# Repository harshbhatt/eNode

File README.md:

# Notes
* Current project files under `Hardware` folder
* Some resistors and capacitors (imported from the photon) don't have a "box" silkscreen in their footprint - for the final batch, these footprints are better omitted.
* RF components have been placed using the photon as reference
  * (X,Y) coords for RF components have been taken from reference design then moved as a group to maintain relative positioning
* (X,Y) coords for the remaining major components can be referenced from V2
* Make sure to use the 4-layer DRC from spark (under photon\cam-drc\spark-4layer.dru)
* Keep all traces at **12mils** unless absolutely needed

# To-Do
* Change MEMs mic to Condenser mic
* Ground plane vias for RF
* Determine good location for RGB LED
* Copy keepout & fill polygons from V2.2 and photon reference
* Source a SMT LDR?
* All remaining RLC footprints can be replaced with the footprints used by spark, or the master library can be updated

* Possibly shorten overall length of sensor -> if all components fit

# General Guide
* Don't commit library, board and schematic backup files auto generated by Eagle (should be taken care of, by the included .gitignore file, but just fyi)
* Look at V2.2 & photon for reference (Under reference drawings folder)
* Make sure you set your library path to the `Libraries` folder under `Options->Directories` in Eagle

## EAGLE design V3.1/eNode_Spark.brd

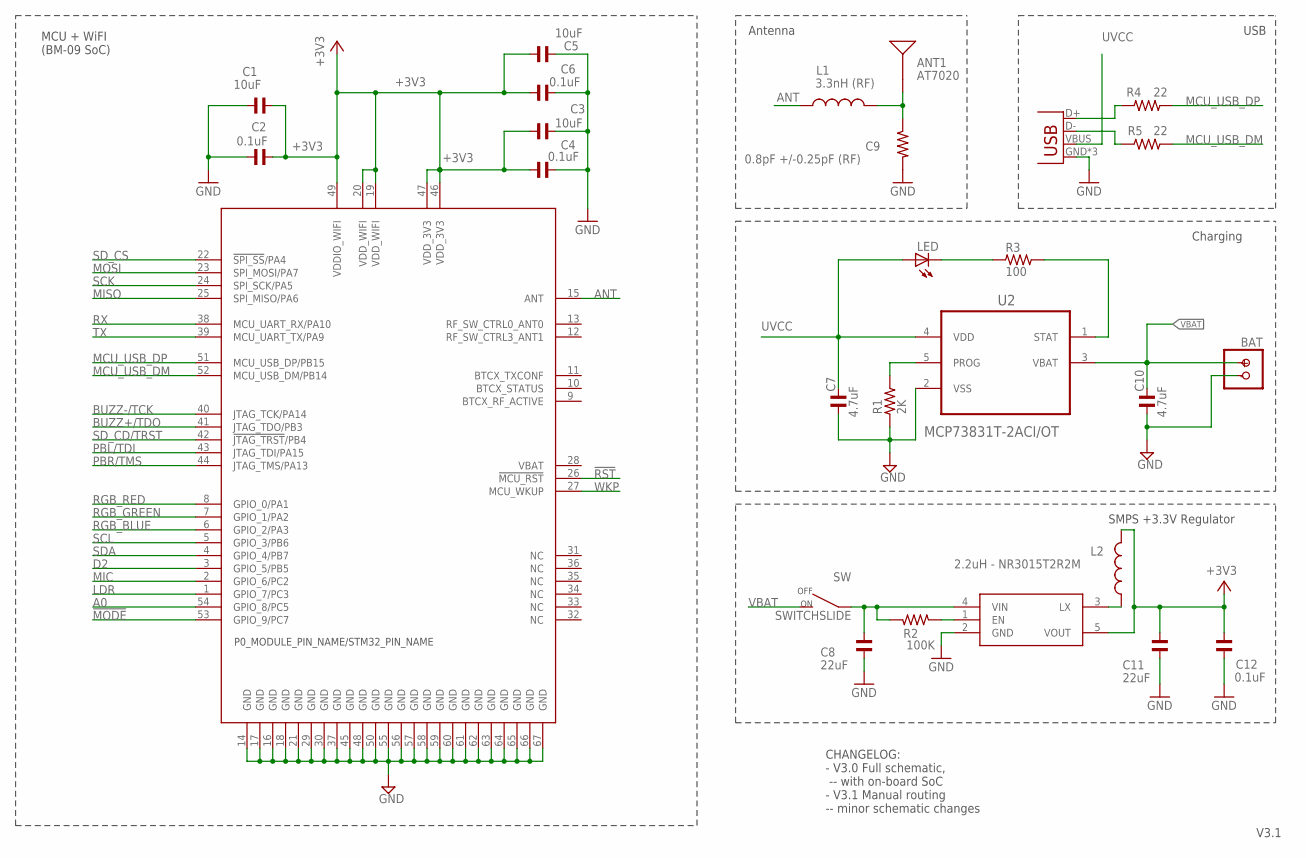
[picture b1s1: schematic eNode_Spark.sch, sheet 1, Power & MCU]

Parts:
ANT1: AT7020
BAT: BATTERYSMT; JST-2-SMD
C1, C3, C5: 10uF; C0402
C2, C4, C6, C12: 0.1uF; C0402
C7, C10: 4.7uF; C0402
C8, C11: 22uF; C0603
C9: 0.8pF +/-0.25pF (RF); R0402_B
L1: 3.3nH (RF); L0402_B
L2: 2.2uH - NR3015T2R2M; INDUCTOR-NR3015
LED: LED; RA_SMD_LED
R1: 2K; R0603
R2: 100K; R0402
R3: 100; R0603
R4, R5: 22; R0402
SW: SWITCHSLIDE; CHANGE_OVER_SLIDE
U1: WM-N-BM-09
U2: MCP73831T-2ACI/OT; SOT95P280X145-5N
U3: R8008-33; SOT23-5
X1: USB-MICROB; USB-MICROB-SLOT-HOLE

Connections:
!MODE: U1.53 (GPIO_9/PC7); also elsewhere on the board
!RST: U1.26 (!MCU_RST); also elsewhere on the board
+3V3: C1.2, C2.2, C3.1, C4.2, C5.1, C6.2, C11.1, C12.1, L2.2, U1.19 (VDD_WIFI), U1.20 (VDD_WIFI), U1.46 (VDD_3V3), U1.47 (VDD_3V3), U1.49 (VDDIO_WIFI), U3.5 (VOUT); also elsewhere on the board
A0: U1.54 (GPIO_8/PC5)
ANT: L1.1, U1.15 (ANT)
BUZZ+/TDO: U1.41 (JTAG_TDO/PB3); also elsewhere on the board
BUZZ-/TCK: U1.40 (JTAG_TCK/PA14); also elsewhere on the board
D2: U1.3 (GPIO_5/PB5)
ENABLE: R2.1, U3.1 (EN)
GND: BAT.-, C1.1, C2.1, C3.2, C4.1, C5.2, C6.1, C7.1, C8.2, C9.2, C10.1, C11.2, C12.2, R1.1, U1.14 (GND), U1.16 (GND), U1.17 (GND), U1.18 (GND), U1.21 (GND), U1.29 (GND), U1.30 (GND), U1.37 (GND), U1.45 (GND), U1.48 (GND), U1.50 (GND), U1.55 (GND), U1.56 (GND), U1.57 (GND), U1.58 (GND), U1.59 (GND), U1.60 (GND), U1.61 (GND), U1.62 (GND), U1.63 (GND), U1.64 (GND), U1.65 (GND), U1.66 (GND), U1.67 (GND), U2.2 (VSS), U3.2 (GND), X1.GND, X1.MT1 (GND), X1.MT2 (GND); also elsewhere on the board
LDR: U1.1 (GPIO_7/PC3); also elsewhere on the board
MCU_USB_DM: R5.1, U1.52 (MCU_USB_DM/PB14)
MCU_USB_DP: R4.1, U1.51 (MCU_USB_DP/PB15)
MIC: U1.2 (GPIO_6/PC2); also elsewhere on the board
MISO: U1.25 (SPI_MISO/PA6); also elsewhere on the board
MOSI: U1.23 (SPI_MOSI/PA7); also elsewhere on the board
unnamed: ANT1.1, C9.1, L1.2
unnamed: C8.1, R2.2, SW.1, U3.4 (VIN)
unnamed: L2.1, U3.3 (LX)
unnamed: R1.2, U2.5 (PROG)
unnamed: LED.C, R3.1
unnamed: R3.2, U2.1 (STAT)
unnamed: R5.2, X1.D-
unnamed: R4.2, X1.D+
PBL/TDI: U1.43 (JTAG_TDI/PA15); also elsewhere on the board
PBR/TMS: U1.44 (JTAG_TMS/PA13); also elsewhere on the board
RGB_BLUE: U1.6 (GPIO_2/PA3); also elsewhere on the board
RGB_GREEN: U1.7 (GPIO_1/PA2); also elsewhere on the board
RGB_RED: U1.8 (GPIO_0/PA1); also elsewhere on the board
RX: U1.38 (MCU_UART_RX/PA10); also elsewhere on the board
SCK: U1.24 (SPI_SCK/PA5); also elsewhere on the board
SCL: U1.5 (GPIO_3/PB6); also elsewhere on the board
SDA: U1.4 (GPIO_4/PB7); also elsewhere on the board
SD_CD/TRST: U1.42 (!JTAG_TRST!/PB4); also elsewhere on the board
SD_CS: U1.22 (!SPI_SS!/PA4); also elsewhere on the board
TX: U1.39 (MCU_UART_TX/PA9); also elsewhere on the board
UVCC: C7.2, LED.A, U2.4 (VDD), X1.VBUS
VBAT: BAT.+, C10.2, SW.2, U2.3 (VBAT)
WKP: U1.27 (MCU_WKUP)

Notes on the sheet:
CHANGELOG: - V3.0 Full schematic, -- with on-board SoC - V3.1 Manual routing -- minor schematic changes
USB
MCU + WiFI (BM-09 SoC)
Charging
Antenna
SMPS +3.3V Regulator

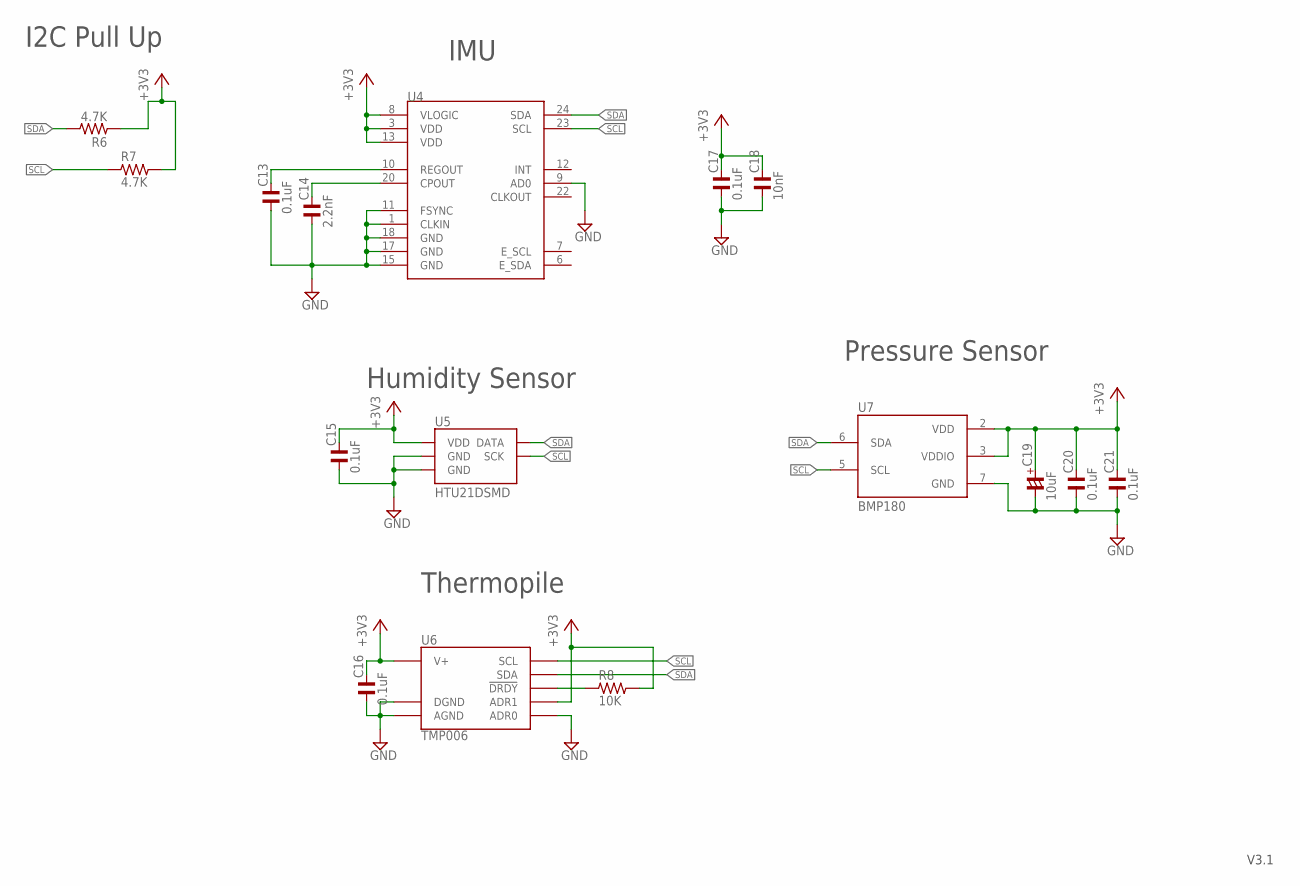
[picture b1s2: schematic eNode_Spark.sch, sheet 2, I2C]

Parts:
C13, C15, C16, C17, C20, C21: 0.1uF; C0402
C14: 2.2nF; C0402
C18: 10nF; C0402
C19: 10uF; C1206/T
R6, R7: 4.7K; R0402
R8: 10K; R0603
U4: MPU-9150QFN-24-NP; QFN-24-NP
U5: HTU21DSMD; HTU21D
U6: TMP006; BGA8DS
U7: BMP180

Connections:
+3V3: C15.2, C16.2, C17.2, C18.2, C19.+, C20.2, C21.2, R6.1, R7.2, R8.2, U4.3 (VDD), U4.8 (VLOGIC), U4.13 (VDD), U5.VDD, U6.A3 (V+), U6.B1 (ADR1), U7.2 (VDD), U7.3 (VDDIO); also elsewhere on the board
GND: C13.1, C14.1, C15.1, C16.1, C17.1, C18.1, C19.-, C20.1, C21.1, U4.1 (CLKIN), U4.9 (AD0), U4.11 (FSYNC), U4.15 (GND), U4.17 (GND), U4.18 (GND), U5.7 (GND), U5.GND, U6.A1 (DGND), U6.A2 (AGND), U6.C1 (ADR0), U7.7 (GND); also elsewhere on the board
unnamed: C14.2, U4.20 (CPOUT)
unnamed: R8.1, U6.C2 (!DRDY)
unnamed: C13.2, U4.10 (REGOUT)
SCL: R7.1, U4.23 (SCL), U5.SCK, U6.B3 (SCL), U7.5 (SCL); also elsewhere on the board
SDA: R6.2, U4.24 (SDA), U5.DATA, U6.C3 (SDA), U7.6 (SDA); also elsewhere on the board

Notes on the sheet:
IMU
Humidity Sensor
Pressure Sensor
Thermopile
I2C Pull Up

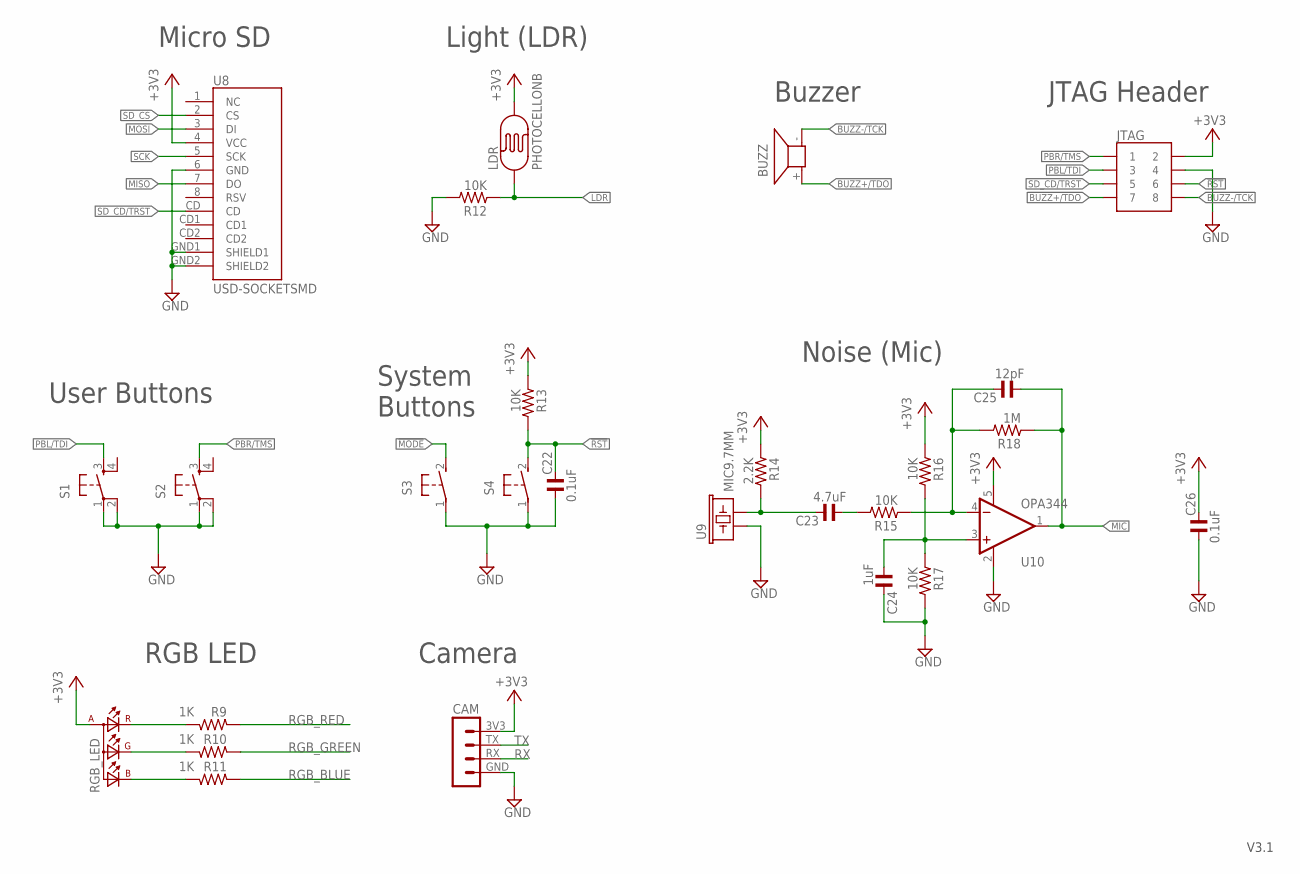
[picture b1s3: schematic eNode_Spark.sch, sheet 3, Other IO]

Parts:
BUZZ: BUZZER; OFFBOARD_NOSIGN
C22, C26: 0.1uF; C0402
C23: 4.7uF; C0402
C24: 1uF; C0402
C25: 12pF; C0402
CAM: MA04-1
JTAG: JTAG_CONNECTOR; JTAG_DIP
LDR: PHOTOCELLONB; ON_BOARD
R9, R10, R11: 1K; R0402
R12: 10K; R0603
R13, R15, R16, R17: 10K; R0402
R14: 2.2K; R0402
R18: 1M; R0402
RGB_LED: TOPLED-3PLCC; P-LCC-4-3
S1, S2: TAC_SWITCH_4SMD; TACTILE_SWITCH_SMD_LARGE_4
S3: MODE; DTSM-3
S4: RESET; DTSM-3
U8: USD-SOCKETSMD; MICRO-SD-SOCKET-PP
U9: MIC9.7MM; MIC-9.7MM
U10: OPA344; SOT23-5

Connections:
!MODE: S3.2; also elsewhere on the board
!RST: C22.2, JTAG.6, R13.2, S4.2; also elsewhere on the board
+3V3: C26.2, CAM.3V3, JTAG.2, LDR.2, R13.1, R14.1, R16.1, RGB_LED.A (A2), U8.4 (VCC), U10.5 (V+); also elsewhere on the board
BUZZ+/TDO: BUZZ.+, JTAG.7; also elsewhere on the board
BUZZ-/TCK: BUZZ.-, JTAG.8; also elsewhere on the board
GND: C22.1, C24.2, C26.1, CAM.GND, JTAG.4, R12.2, R17.2, S1.1, S1.2, S2.1, S2.2, S3.1, S4.1, U8.6 (GND), U8.GND1 (SHIELD1), U8.GND2 (SHIELD2), U9.1, U10.2 (V-); also elsewhere on the board
LDR: LDR.1, R12.1; also elsewhere on the board
MIC: C25.1, R18.1, U10.1 (OUT); also elsewhere on the board
MISO: U8.7 (DO); also elsewhere on the board
MOSI: U8.3 (DI); also elsewhere on the board
unnamed: C23.1, R15.2
unnamed: C25.2, R15.1, R18.2, U10.4 (-IN)
unnamed: C24.1, R16.2, R17.1, U10.3 (+IN)
unnamed: C23.2, R14.2, U9.2
unnamed: R10.1, RGB_LED.G (CGREEN)
unnamed: R11.1, RGB_LED.B (CBLUE)
unnamed: R9.1, RGB_LED.R (CRED)
PBL/TDI: JTAG.3, S1.3; also elsewhere on the board
PBR/TMS: JTAG.1, S2.3; also elsewhere on the board
RGB_BLUE: R11.2; also elsewhere on the board
RGB_GREEN: R10.2; also elsewhere on the board
RGB_RED: R9.2; also elsewhere on the board
RX: CAM.RX; also elsewhere on the board
SCK: U8.5 (SCK); also elsewhere on the board
SD_CD/TRST: JTAG.5, U8.CD; also elsewhere on the board
SD_CS: U8.2 (CS); also elsewhere on the board
TX: CAM.TX; also elsewhere on the board

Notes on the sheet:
Micro SD
User Buttons
Light (LDR)
Buzzer
Noise (Mic)
RGB LED
Camera
System Buttons
JTAG Header

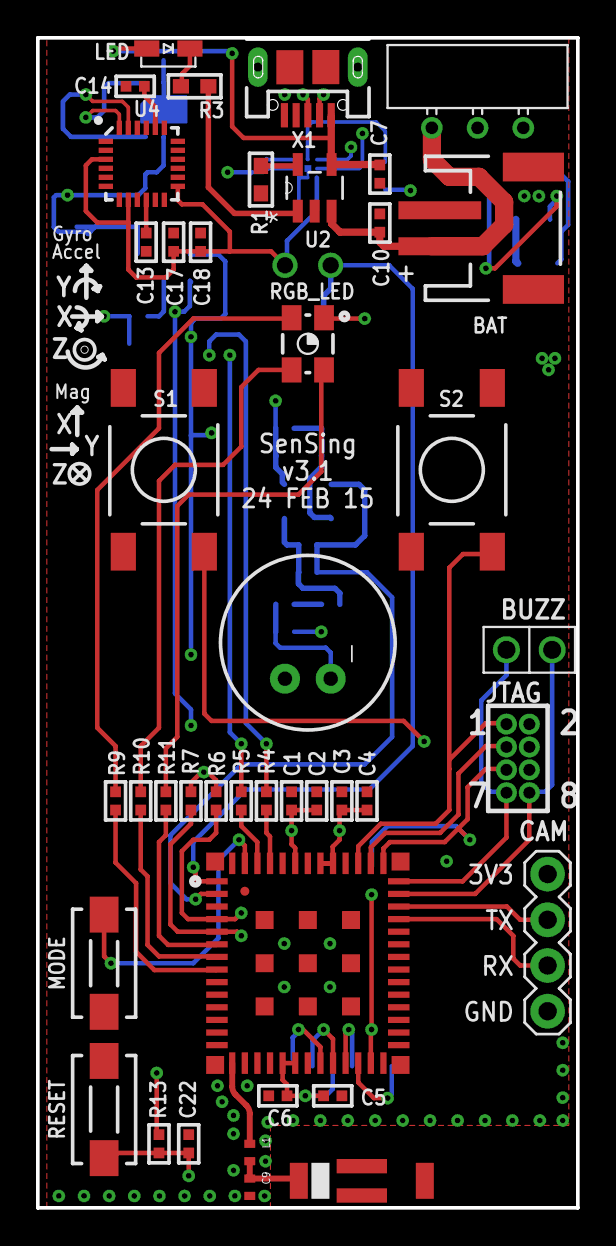
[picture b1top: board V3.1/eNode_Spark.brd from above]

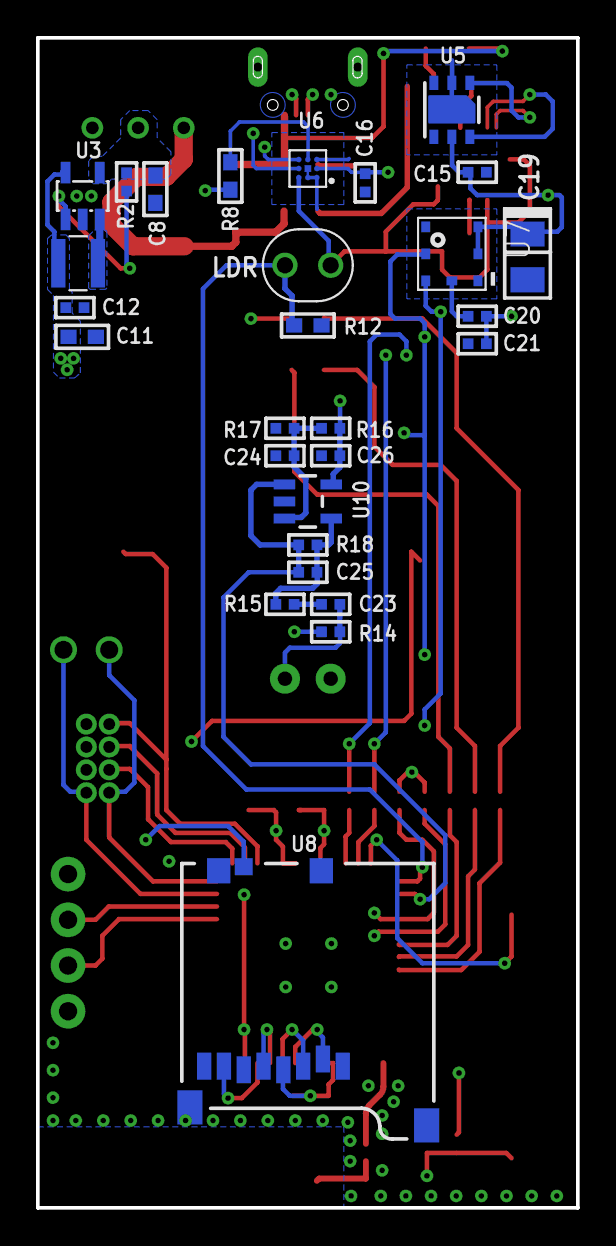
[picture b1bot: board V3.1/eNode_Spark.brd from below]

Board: 4 copper layers, 30.0 x 65.0 mm, 70 parts (28 on the bottom side), 46 nets.

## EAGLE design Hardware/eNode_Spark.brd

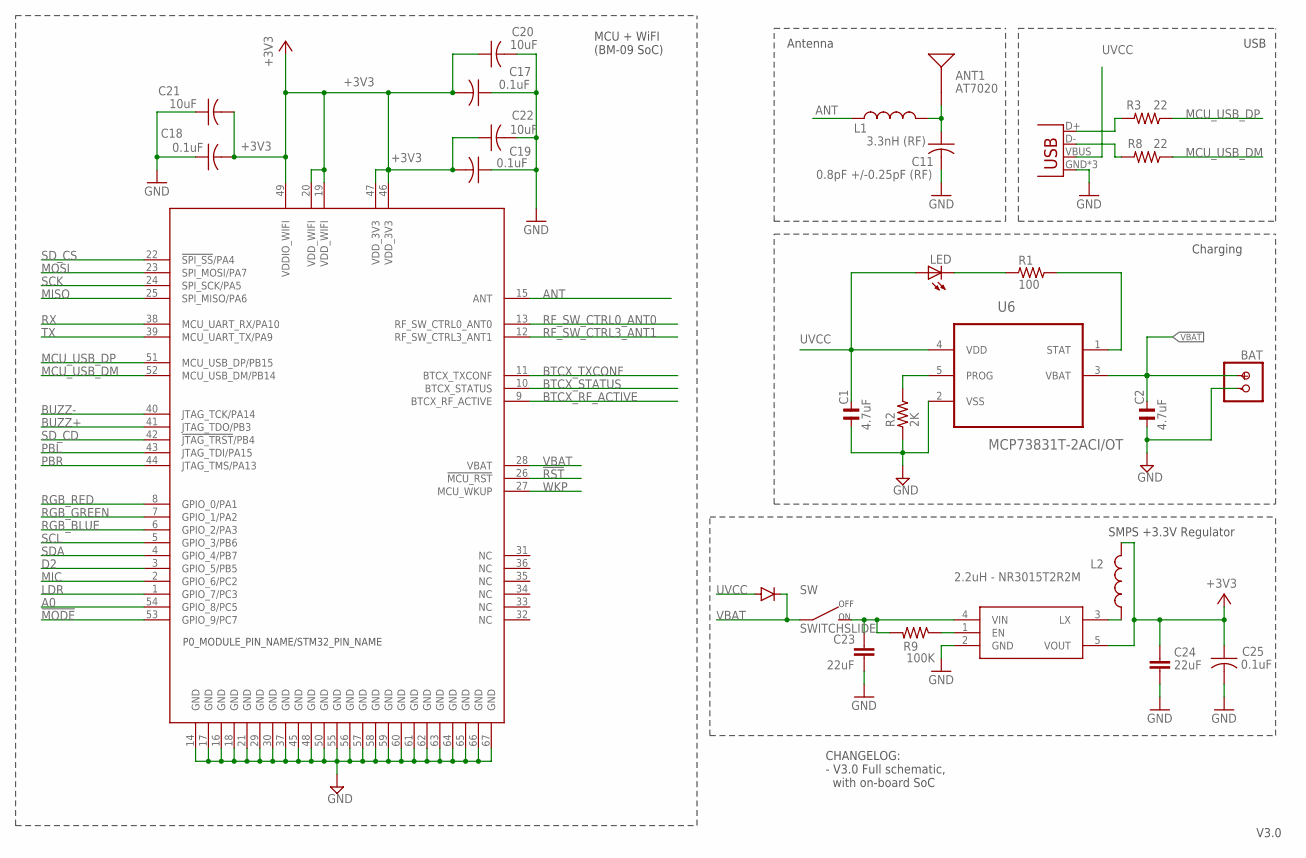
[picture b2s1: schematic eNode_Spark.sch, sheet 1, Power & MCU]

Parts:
ANT1: AT7020
BAT: BATTERYSMT; JST-2-SMD
C1, C2: 4.7uF; C0402
C11: 0.8pF +/-0.25pF (RF); C0402_B
C17, C18, C19: 0.1uF; C0402_B
C20, C21, C22: 10uF; C0402_B
C23, C24: 22uF; C0603
C25: 0.1uF; C0402
D1: DIODE; DIODE-DO-220AA(SMP)
L1: 3.3nH (RF); L0402_B
L2: 2.2uH - NR3015T2R2M; INDUCTOR-NR3015
LED: LED; RA_SMD_LED
R1: 100; R0603
R2: 2K; R0603
R3, R8: 22; R0402_B
R9: 100K; R0402_B
SW: SWITCHSLIDE; CHANGE_OVER_SLIDE
U6: MCP73831T-2ACI/OT; SOT95P280X145-5N
U10: WM-N-BM-09
U$7: R8008-33; SOT23-5
X1: USB-MICROB; USB-MICROB-SLOT-HOLE

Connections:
!MODE: U10.53 (GPIO_9/PC7)
!RST: U10.26 (!MCU_RST)
+3V3: C17.2, C18.2, C19.2, C20.1, C21.2, C22.1, C24.1, C25.1, L2.2, U10.19 (VDD_WIFI), U10.20 (VDD_WIFI), U10.46 (VDD_3V3), U10.47 (VDD_3V3), U10.49 (VDDIO_WIFI), U$7.5 (VOUT); also elsewhere on the board
A0: U10.54 (GPIO_8/PC5)
ANT: L1.1, U10.15 (ANT)
BTCX_RF_ACTIVE: U10.9 (BTCX_RF_ACTIVE)
BTCX_STATUS: U10.10 (BTCX_STATUS)
BTCX_TXCONF: U10.11 (BTCX_TXCONF)
BUZZ+: U10.41 (JTAG_TDO/PB3); also elsewhere on the board
BUZZ-: U10.40 (JTAG_TCK/PA14); also elsewhere on the board
D2: U10.3 (GPIO_5/PB5)
ENABLE: R9.1, U$7.1 (EN)
GND: BAT.-, C1.1, C2.1, C11.2, C17.1, C18.1, C19.1, C20.2, C21.1, C22.2, C23.2, C24.2, C25.2, R2.1, U6.2 (VSS), U10.14 (GND), U10.16 (GND), U10.17 (GND), U10.18 (GND), U10.21 (GND), U10.29 (GND), U10.30 (GND), U10.37 (GND), U10.45 (GND), U10.48 (GND), U10.50 (GND), U10.55 (GND), U10.56 (GND), U10.57 (GND), U10.58 (GND), U10.59 (GND), U10.60 (GND), U10.61 (GND), U10.62 (GND), U10.63 (GND), U10.64 (GND), U10.65 (GND), U10.66 (GND), U10.67 (GND), U$7.2 (GND), X1.GND, X1.MT1 (GND), X1.MT2 (GND); also elsewhere on the board
LDR: U10.1 (GPIO_7/PC3); also elsewhere on the board
MCU_USB_DM: R8.1, U10.52 (MCU_USB_DM/PB14)
MCU_USB_DP: R3.1, U10.51 (MCU_USB_DP/PB15)
MIC: U10.2 (GPIO_6/PC2); also elsewhere on the board
MISO: U10.25 (SPI_MISO/PA6); also elsewhere on the board
MOSI: U10.23 (SPI_MOSI/PA7); also elsewhere on the board
unnamed: ANT1.1, C11.1, L1.2
unnamed: L2.1, U$7.3 (LX)
unnamed: R2.2, U6.5 (PROG)
unnamed: LED.C, R1.1
unnamed: R1.2, U6.1 (STAT)
unnamed: R8.2, X1.D-
unnamed: R3.2, X1.D+
PBL: U10.43 (JTAG_TDI/PA15); also elsewhere on the board
PBR: U10.44 (JTAG_TMS/PA13); also elsewhere on the board
RF_SW_CTRL0_ANT0: U10.13 (RF_SW_CTRL0_ANT0)
RF_SW_CTRL3_ANT1: U10.12 (RF_SW_CTRL3_ANT1)
RGB_BLUE: U10.6 (GPIO_2/PA3); also elsewhere on the board
RGB_GREEN: U10.7 (GPIO_1/PA2); also elsewhere on the board
RGB_RED: U10.8 (GPIO_0/PA1); also elsewhere on the board
RX: U10.38 (MCU_UART_RX/PA10); also elsewhere on the board
SCK: U10.24 (SPI_SCK/PA5); also elsewhere on the board
SCL: U10.5 (GPIO_3/PB6); also elsewhere on the board
SDA: U10.4 (GPIO_4/PB7); also elsewhere on the board
SD_CD: U10.42 (!JTAG_TRST!/PB4); also elsewhere on the board
SD_CS: U10.22 (!SPI_SS!/PA4); also elsewhere on the board
TX: U10.39 (MCU_UART_TX/PA9); also elsewhere on the board
UVCC: C1.2, D1.ANODE, LED.A, U6.4 (VDD), X1.VBUS
VBAT: BAT.+, C2.2, C23.1, D1.CATHODE, R9.2, SW.1, SW.2, U6.3 (VBAT), U10.28 (VBAT), U$7.4 (VIN)
WKP: U10.27 (MCU_WKUP)

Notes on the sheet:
V3.0
CHANGELOG: - V3.0 Full schematic, with on-board SoC
USB
MCU + WiFI (BM-09 SoC)
Charging
Antenna
SMPS +3.3V Regulator

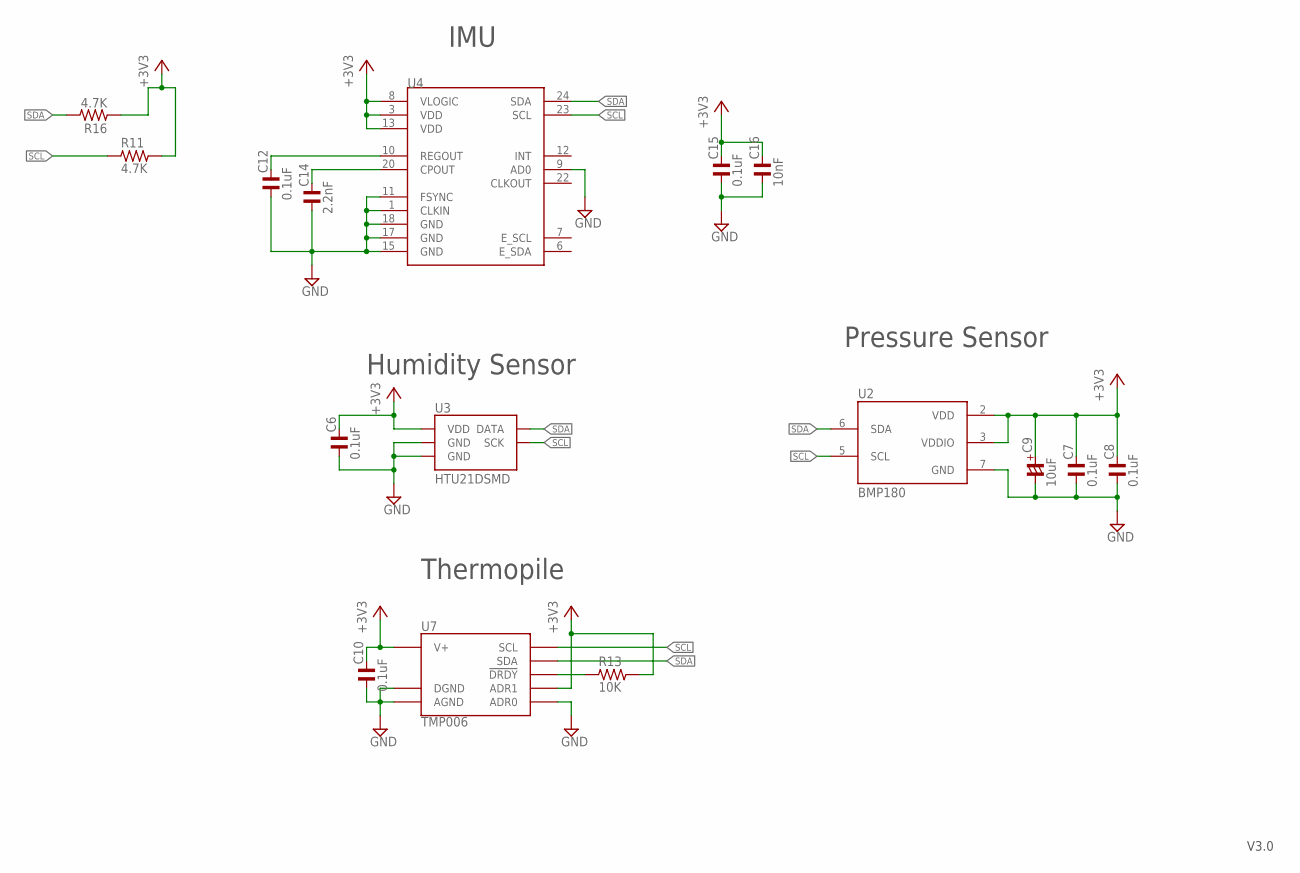
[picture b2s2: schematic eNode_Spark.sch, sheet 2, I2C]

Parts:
C6, C7, C8, C10, C12, C15: 0.1uF; C0402
C9: 10uF; C1206/T
C14: 2.2nF; C0402
C16: 10nF; C0402
R11, R16: 4.7K; R0603
R13: 10K; R0603
U2: BMP180
U3: HTU21DSMD; HTU21D
U4: MPU-9150QFN-24-NP; QFN-24-NP
U7: TMP006; BGA8DS

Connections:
+3V3: C6.2, C7.2, C8.2, C9.+, C10.2, C15.2, C16.2, R11.2, R13.2, R16.1, U2.2 (VDD), U2.3 (VDDIO), U3.VDD, U4.3 (VDD), U4.8 (VLOGIC), U4.13 (VDD), U7.A3 (V+), U7.B1 (ADR1); also elsewhere on the board
GND: C6.1, C7.1, C8.1, C9.-, C10.1, C12.1, C14.1, C15.1, C16.1, U2.7 (GND), U3.7 (GND), U3.GND, U4.1 (CLKIN), U4.9 (AD0), U4.11 (FSYNC), U4.15 (GND), U4.17 (GND), U4.18 (GND), U7.A1 (DGND), U7.A2 (AGND), U7.C1 (ADR0); also elsewhere on the board
unnamed: C14.2, U4.20 (CPOUT)
unnamed: R13.1, U7.C2 (!DRDY)
unnamed: C12.2, U4.10 (REGOUT)
SCL: R11.1, U2.5 (SCL), U3.SCK, U4.23 (SCL), U7.B3 (SCL); also elsewhere on the board
SDA: R16.2, U2.6 (SDA), U3.DATA, U4.24 (SDA), U7.C3 (SDA); also elsewhere on the board

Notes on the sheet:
IMU
Humidity Sensor
Pressure Sensor
Thermopile
V3.0

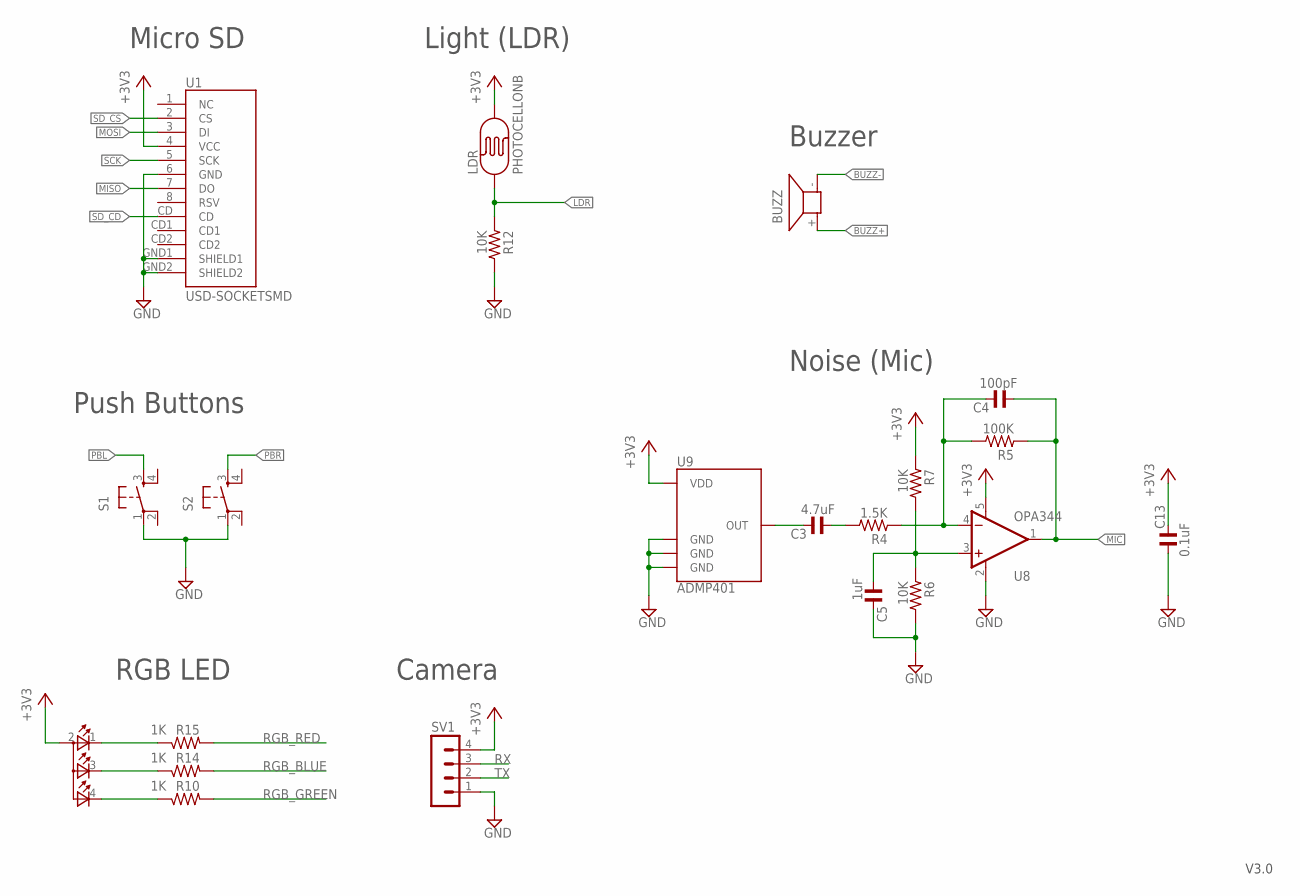
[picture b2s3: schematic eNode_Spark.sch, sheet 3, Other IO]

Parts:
BUZZ: BUZZER; OFFBOARD_NOSIGN
C3: 4.7uF; C0402
C4: 100pF; C0402
C5: 1uF; C0402
C13: 0.1uF; C0402
LDR: PHOTOCELLONB; ON_BOARD
LED2: CREE_CLVBA-FKA; P-LCC-4-3
R4: 1.5K; R0402
R5: 100K; R0402
R6, R7: 10K; R0402
R10, R14, R15: 1K; R0402_B
R12: 10K; R0603
S1, S2: TAC_SWITCHSMD; TACTILE_SWITCH_SMD
SV1: MA04-1
U1: USD-SOCKETSMD; MICRO-SD-SOCKET-PP
U8: OPA344; SOT23-5
U9: ADMP401

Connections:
+3V3: C13.2, LDR.2, LED2.2 (A2), R7.1, SV1.4, U1.4 (VCC), U8.5 (V+), U9.5 (VDD); also elsewhere on the board
BUZZ+: BUZZ.+; also elsewhere on the board
BUZZ-: BUZZ.-; also elsewhere on the board
GND: C5.2, C13.1, R6.2, R12.2, S1.1, S2.1, SV1.1, U1.6 (GND), U1.GND1 (SHIELD1), U1.GND2 (SHIELD2), U8.2 (V-), U9.2 (GND), U9.4 (GND), U9.6 (GND); also elsewhere on the board
LDR: LDR.1, R12.1; also elsewhere on the board
MIC: C4.1, R5.1, U8.1 (OUT); also elsewhere on the board
MISO: U1.7 (DO); also elsewhere on the board
MOSI: U1.3 (DI); also elsewhere on the board
unnamed: C3.2, U9.1 (OUT)
unnamed: C3.1, R4.2
unnamed: C4.2, R4.1, R5.2, U8.4 (-IN)
unnamed: C5.1, R6.1, R7.2, U8.3 (+IN)
unnamed: LED2.3 (CBLUE), R14.1
unnamed: LED2.4 (CGREEN), R10.1
unnamed: LED2.1 (CRED), R15.1
PBL: S1.3; also elsewhere on the board
PBR: S2.3; also elsewhere on the board
RGB_BLUE: R14.2; also elsewhere on the board
RGB_GREEN: R10.2; also elsewhere on the board
RGB_RED: R15.2; also elsewhere on the board
RX: SV1.3; also elsewhere on the board
SCK: U1.5 (SCK); also elsewhere on the board
SD_CD: U1.CD; also elsewhere on the board
SD_CS: U1.2 (CS); also elsewhere on the board
TX: SV1.2; also elsewhere on the board

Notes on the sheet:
Micro SD
Push Buttons
Light (LDR)
Buzzer
Noise (Mic)
V3.0
RGB LED
Camera

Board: 4 copper layers, 65 parts (4 on the bottom side), 43 nets, no tracks yet.

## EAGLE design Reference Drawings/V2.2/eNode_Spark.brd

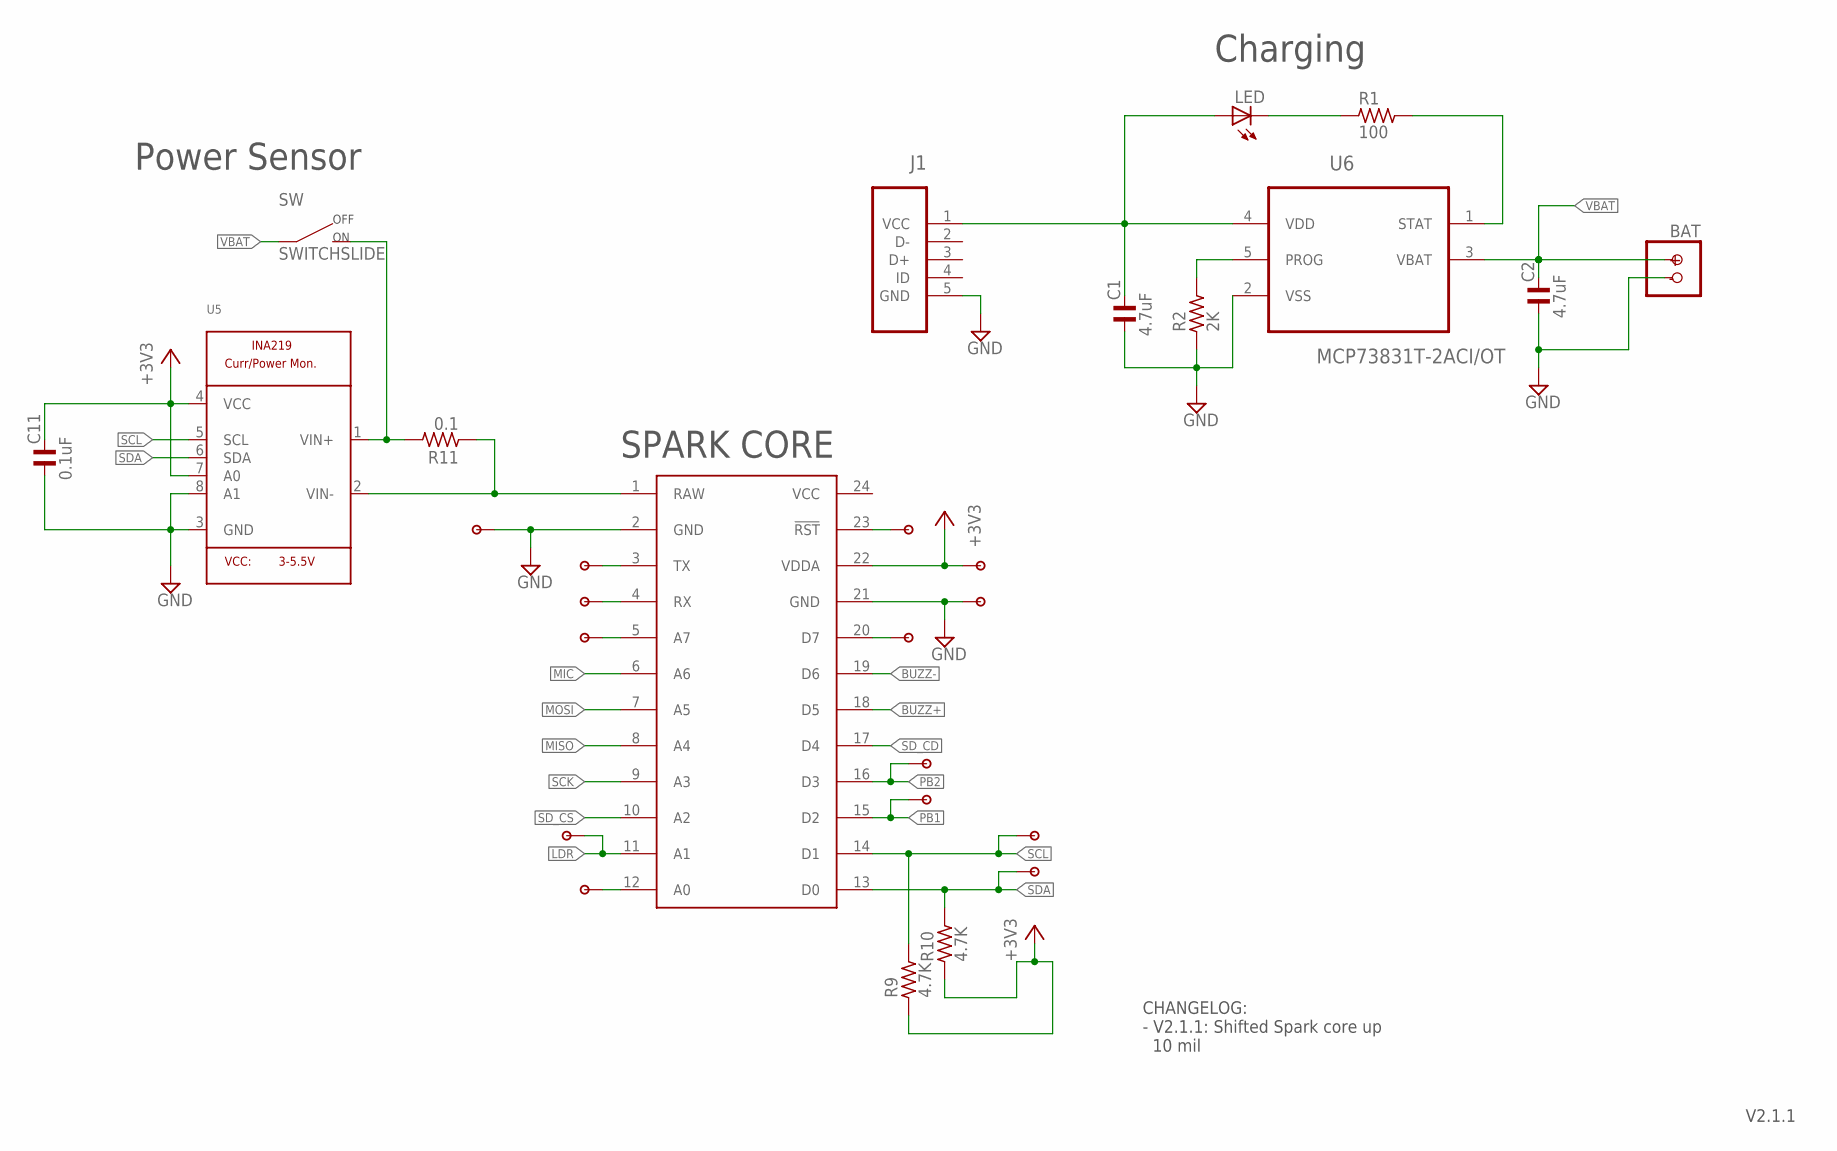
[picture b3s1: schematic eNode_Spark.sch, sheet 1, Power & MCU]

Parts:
BAT: BATTERYSMT; JST-2-SMD
C1, C2: 4.7uF; C0402
C11: 0.1uF; C0402
J1: 47346-0001; MOLEX_47346-0001
LED: LED; RA_SMD_LED
R1: 100; R0603
R2: 2K; R0603
R9, R10: 4.7K; R0603
R11: 0.1; R2512
SPARK: SPARK_CORECORE; SPARK_CORE
SW: SWITCHSLIDE; CHANGE_OVER_SLIDE
U5: INA219; SOT23-8
U6: MCP73831T-2ACI/OT; SOT95P280X145-5N
U$1, U$2, U$6, U$7, U$8, U$9, U$10, U$11, U$12, U$13, U$14, U$15, U$16, U$17: 1PIN

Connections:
+3V3: C11.2, R9.1, R10.1, SPARK.22 (VDDA), U5.4 (VCC), U5.7 (A0), U$6.P$1; also elsewhere on the board
BUZZ+: SPARK.18 (D5); also elsewhere on the board
BUZZ-: SPARK.19 (D6); also elsewhere on the board
GND: BAT.-, C1.1, C2.1, C11.1, J1.5 (GND), R2.1, SPARK.2 (GND), SPARK.21 (GND), U5.3 (GND), U5.8 (A1), U6.2 (VSS), U$11.P$1, U$17.P$1; also elsewhere on the board
LDR: SPARK.11 (A1), U$16.P$1; also elsewhere on the board
MIC: SPARK.6 (A6); also elsewhere on the board
MISO: SPARK.8 (A4); also elsewhere on the board
MOSI: SPARK.7 (A5); also elsewhere on the board
unnamed: C1.2, J1.1 (VCC), LED.A, U6.4 (VDD)
unnamed: R11.1, SPARK.1 (RAW), U5.2 (VIN-)
unnamed: R2.2, U6.5 (PROG)
unnamed: LED.C, R1.1
unnamed: R1.2, U6.1 (STAT)
unnamed: SPARK.5 (A7), U$2.P$1
unnamed: R11.2, SW.2, U5.1 (VIN+)
unnamed: SPARK.20 (D7), U$10.P$1
unnamed: SPARK.12 (A0), U$1.P$1
unnamed: SPARK.3 (TX), U$12.P$1
unnamed: SPARK.4 (RX), U$13.P$1
unnamed: SPARK.23 (!RST), U$14.P$1
PB1: SPARK.15 (D2), U$9.P$1; also elsewhere on the board
PB2: SPARK.16 (D3), U$15.P$1; also elsewhere on the board
SCK: SPARK.9 (A3); also elsewhere on the board
SCL: R9.2, SPARK.14 (D1), U5.5 (SCL), U$7.P$1; also elsewhere on the board
SDA: R10.2, SPARK.13 (D0), U5.6 (SDA), U$8.P$1; also elsewhere on the board
SD_CD: SPARK.17 (D4); also elsewhere on the board
SD_CS: SPARK.10 (A2); also elsewhere on the board
VBAT: BAT.+, C2.2, SW.1, U6.3 (VBAT)
VCC: SPARK.24 (VCC)

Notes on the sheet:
SPARK CORE
Charging
Power Sensor
V2.1.1
CHANGELOG: - V2.1.1: Shifted Spark core up 10 mil

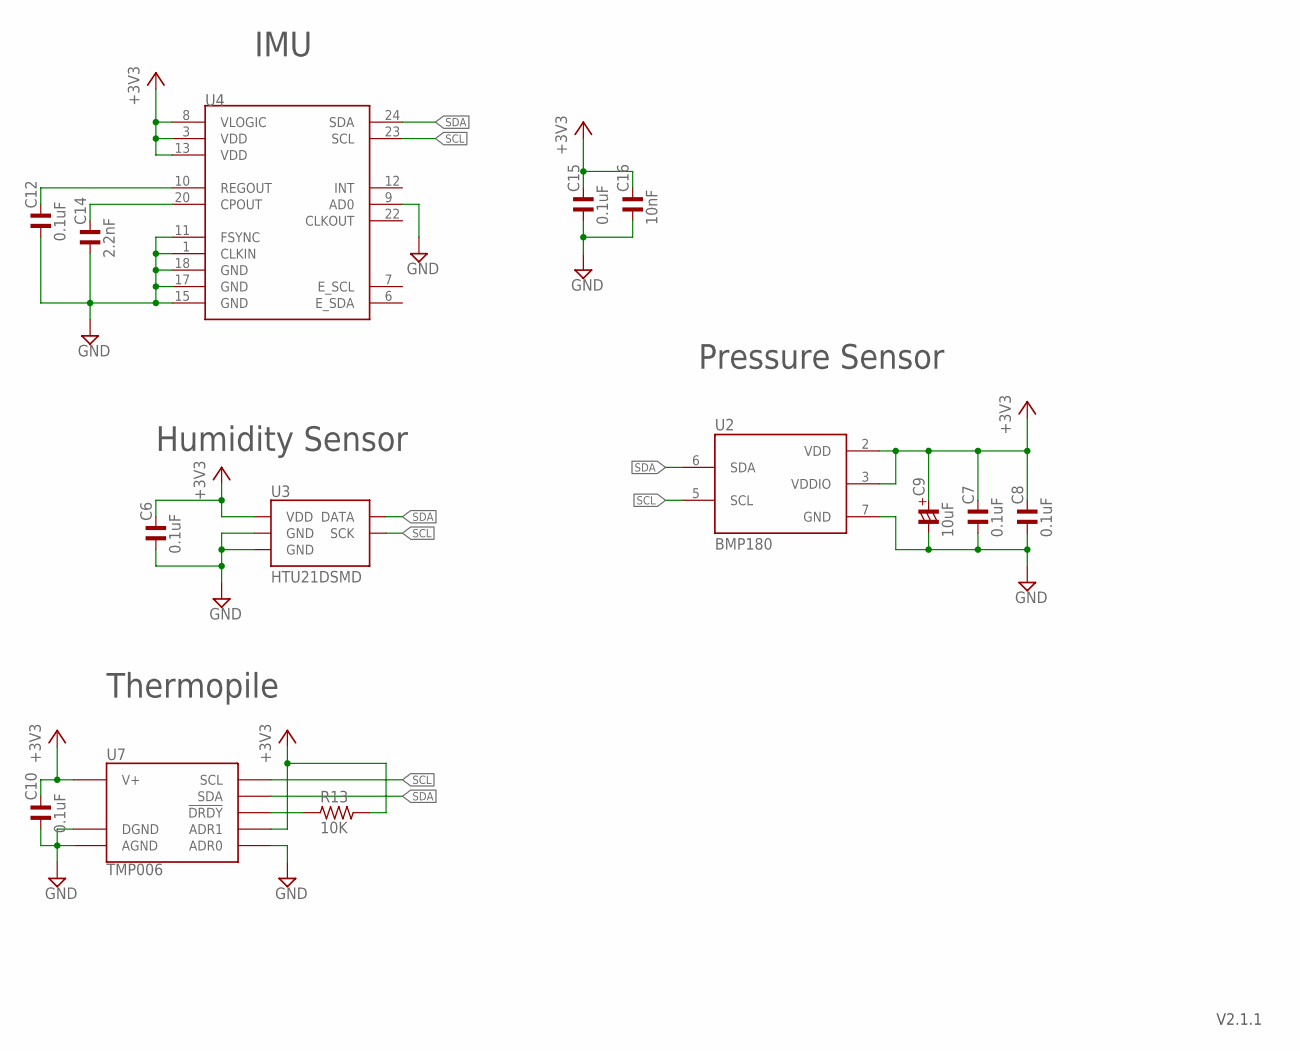
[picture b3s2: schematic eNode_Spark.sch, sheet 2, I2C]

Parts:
C6, C7, C8, C10, C12, C15: 0.1uF; C0402
C9: 10uF; C1206/T
C14: 2.2nF; C0402
C16: 10nF; C0402
R13: 10K; R0603
U2: BMP180
U3: HTU21DSMD; HTU21D
U4: MPU-9150QFN-24-NP; QFN-24-NP
U7: TMP006; BGA8DS

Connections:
+3V3: C6.2, C7.2, C8.2, C9.+, C10.2, C15.2, C16.2, R13.2, U2.2 (VDD), U2.3 (VDDIO), U3.VDD, U4.3 (VDD), U4.8 (VLOGIC), U4.13 (VDD), U7.A3 (V+), U7.B1 (ADR1); also elsewhere on the board
GND: C6.1, C7.1, C8.1, C9.-, C10.1, C12.1, C14.1, C15.1, C16.1, U2.7 (GND), U3.7 (GND), U3.GND, U4.1 (CLKIN), U4.9 (AD0), U4.11 (FSYNC), U4.15 (GND), U4.17 (GND), U4.18 (GND), U7.A1 (DGND), U7.A2 (AGND), U7.C1 (ADR0); also elsewhere on the board
unnamed: C14.2, U4.20 (CPOUT)
unnamed: R13.1, U7.C2 (!DRDY)
unnamed: C12.2, U4.10 (REGOUT)
SCL: U2.5 (SCL), U3.SCK, U4.23 (SCL), U7.B3 (SCL); also elsewhere on the board
SDA: U2.6 (SDA), U3.DATA, U4.24 (SDA), U7.C3 (SDA); also elsewhere on the board

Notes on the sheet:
IMU
Humidity Sensor
Pressure Sensor
Thermopile
V2.1.1

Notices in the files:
parts and their libraries:
rc-master-smd: Copyright (C) 2007-2008, Bob Starr
